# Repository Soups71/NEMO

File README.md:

# NEMO Documentation

Welcome to NEMO—the **NMEA2000 Education and Maritime Operations Platform**.

NEMO is a research platform for exploring at maritime network security. It simulates sensors, sniffs traffic, and demonstrates just how easy you can mess with NMEA2000.

This platform focuses on lowering the bar for getting started with boat hacking. Typically to get started with boat hacking you would need thousands of dollars worth of equipment or a friend with a boat. Thankfully, with NEMO all you need is about 40 dollars.

## What's In Here

### Getting Your Feet Wet
1. **[Project Overview](Documentation/README.md)** - What this is and why boats need better security
2. **[Getting Started](Documentation/Getting_Started.md)** - From zero to flashing firmware
3. **[Operations Guide](Documentation/Operations_Guide.md)** - How to actually use the thing
4. **[FAQ](Documentation/FAQ.md)** - "Why doesn't X work?" answered here

### Understanding the Protocols
1. **[NMEA2000 Protocol](Documentation/NMEA2000.md)** - The marine standard for device communication

### Hardware
1. **[Design Reference](Documentation/PCB_Design.md)** - Schematics, layout, gerbers
2. **[3-D Printed Case](Documentation/Case_Design.md)** - Documentation on the case

### Software
9. **[Source Code Architecture](Documentation/Source_Code_Architecture.md)** - Deep dive into the firmware

### The Fun Part
10. **[Security Research & Attacks](Documentation/Attacks.md)** - How the attacks work and academic context

## Quick Start (TL;DR)

1. Get parts from [Hardware Guide](Documentation/PCB_Design.md)
2. Flash firmware via [Getting Started](Documentation/Getting_Started.md)
3. Learn the UI in [Operations Guide](Documentation/Operations_Guide.md)
4. Break Stuff
5. Profit!

## What This Is For

NEMO exists for:
- **Security researchers** exploring maritime vulnerabilities
- **Students** learning about CAN bus and protocol weaknesses
- **Industry folks** who want to see why NMEA2000 security matters

## Contributing

Found a bug? Got a cool feature idea? Open an issue or send a PR.

Contribution Ideas:
- New PGN support
- Bug fixes
- Documentation improvements

## Contact

Any questions or concerns regarding this project can be sent to nemo@jamescampbell.org

## Disclaimer

Released for educational and research purposes. Don't do crimes with it.

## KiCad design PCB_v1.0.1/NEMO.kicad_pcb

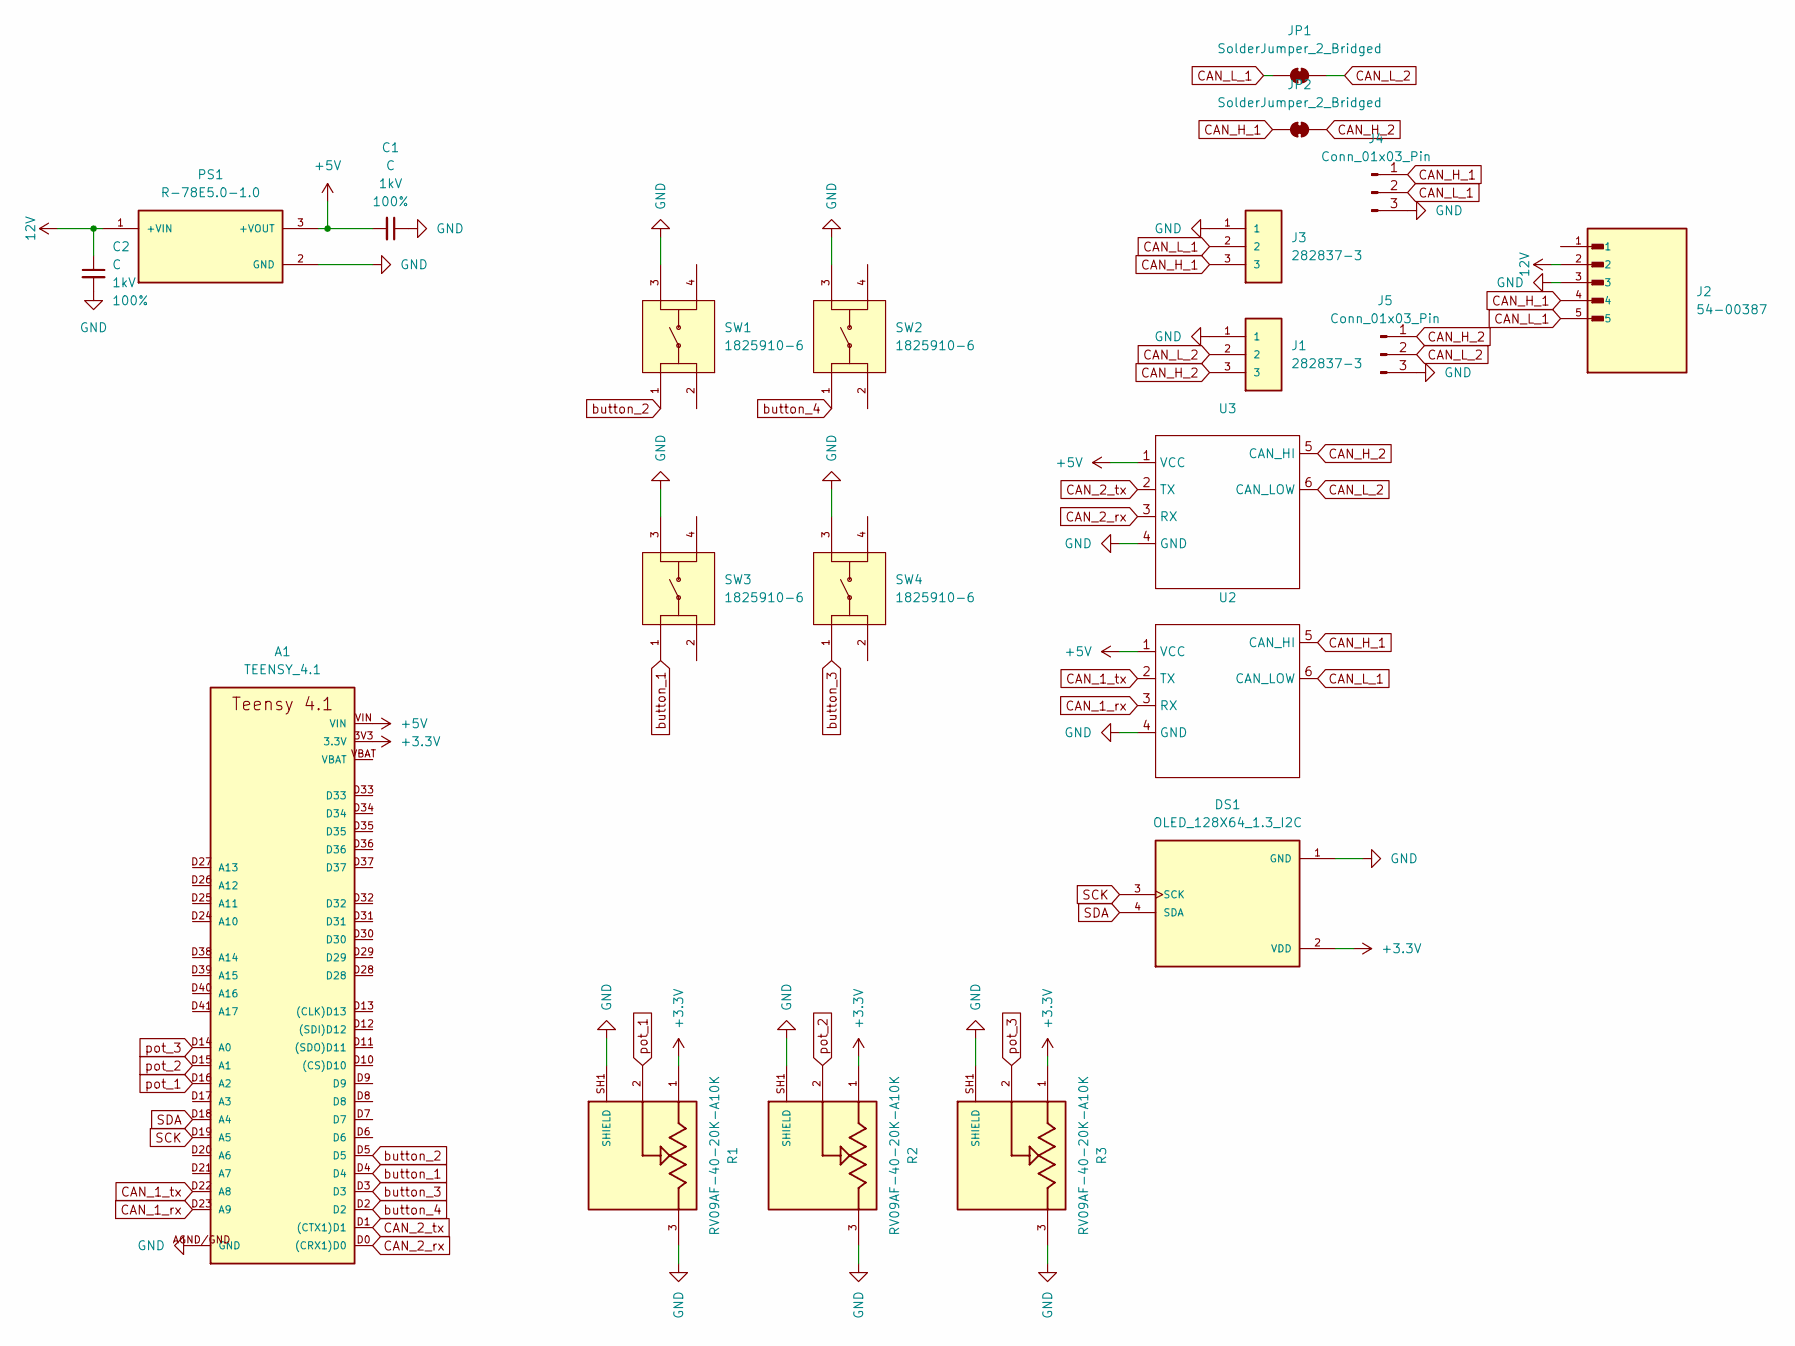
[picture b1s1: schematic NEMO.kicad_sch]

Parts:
A1: TEENSY_4.1; TEENSY_LONG_EXT
C1, C2: C; C_Disc_D9.0mm_W5.0mm_P5.00mm; Voltage 1kV; Tolerance 100%
DS1: OLED_128X64_1.3_I2C; LCD_OLED_128X64_1.3_I2C; PARTREV NA
J1, J3: 282837-3; TE_282837-3; PARTREV H
J2: 54-00387; NMEA2000; PARTREV A
J4, J5: Conn_01x03_Pin; FanPinHeader_1x03_P2.54mm_Vertical
JP1, JP2: SolderJumper_2_Bridged; SolderJumper-2_P1.3mm_Bridged_Pad1.0x1.5mm
PS1: R-78E5.0-1.0; CONV_R-78E5.0-1.0; PARTREV 6
R1, R2, R3: RV09AF-40-20K-A10K; TRIM_RV09AF-40-20K-A10K; PARTREV N/A
SW1, SW2, SW3, SW4: 1825910-6; SW_1825910-6-4; PARTREV C10
U2, U3: CAN_CHIP

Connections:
12V: C2.1, J2.2, PS1.1 (+VIN)
+3.3V: A1.3V3 (3.3V), A1.3V3@2 (3.3V), A1.3V3@3 (3.3V), DS1.2 (VDD), R1.1, R2.1, R3.1
+5V: A1.VIN, C1.2, PS1.3 (+VOUT), U2.1 (VCC), U3.1 (VCC)
CAN_1_rx: A1.D23 (A9), U2.3 (RX)
CAN_1_tx: A1.D22 (A8), U2.2 (TX)
CAN_2_rx: A1.D0 ((CRX1)D0), U3.3 (RX)
CAN_2_tx: A1.D1 ((CTX1)D1), U3.2 (TX)
CAN_H_1: J2.4, J3.3, J4.1, JP2.1 (A), U2.5 (CAN_HI)
CAN_H_2: J1.3, J5.1, JP2.2 (B), U3.5 (CAN_HI)
CAN_L_1: J2.5, J3.2, J4.2, JP1.1 (A), U2.6 (CAN_LOW)
CAN_L_2: J1.2, J5.2, JP1.2 (B), U3.6 (CAN_LOW)
GND: A1.AGND/GND (GND), A1.GND, A1.GND@2 (GND), C1.1, C2.2, DS1.1 (GND), J1.1, J2.3, J3.1, J4.3, J5.3, PS1.2 (GND), R1.3, R1.SH1 (SHIELD), R1.SH2 (SHIELD), R2.3, R2.SH1 (SHIELD), R2.SH2 (SHIELD), R3.3, R3.SH1 (SHIELD), R3.SH2 (SHIELD), SW1.3, SW2.3, SW3.3, SW4.3, U2.4 (GND), U3.4 (GND)
SCK: A1.D19 (A5), DS1.3 (SCK)
SDA: A1.D18 (A4), DS1.4 (SDA)
button_1: A1.D4, SW3.1
button_2: A1.D5, SW1.1
button_3: A1.D3, SW4.1
button_4: A1.D2, SW2.1
pot_1: A1.D16 (A2), R1.2
pot_2: A1.D15 (A1), R2.2
pot_3: A1.D14 (A0), R3.2

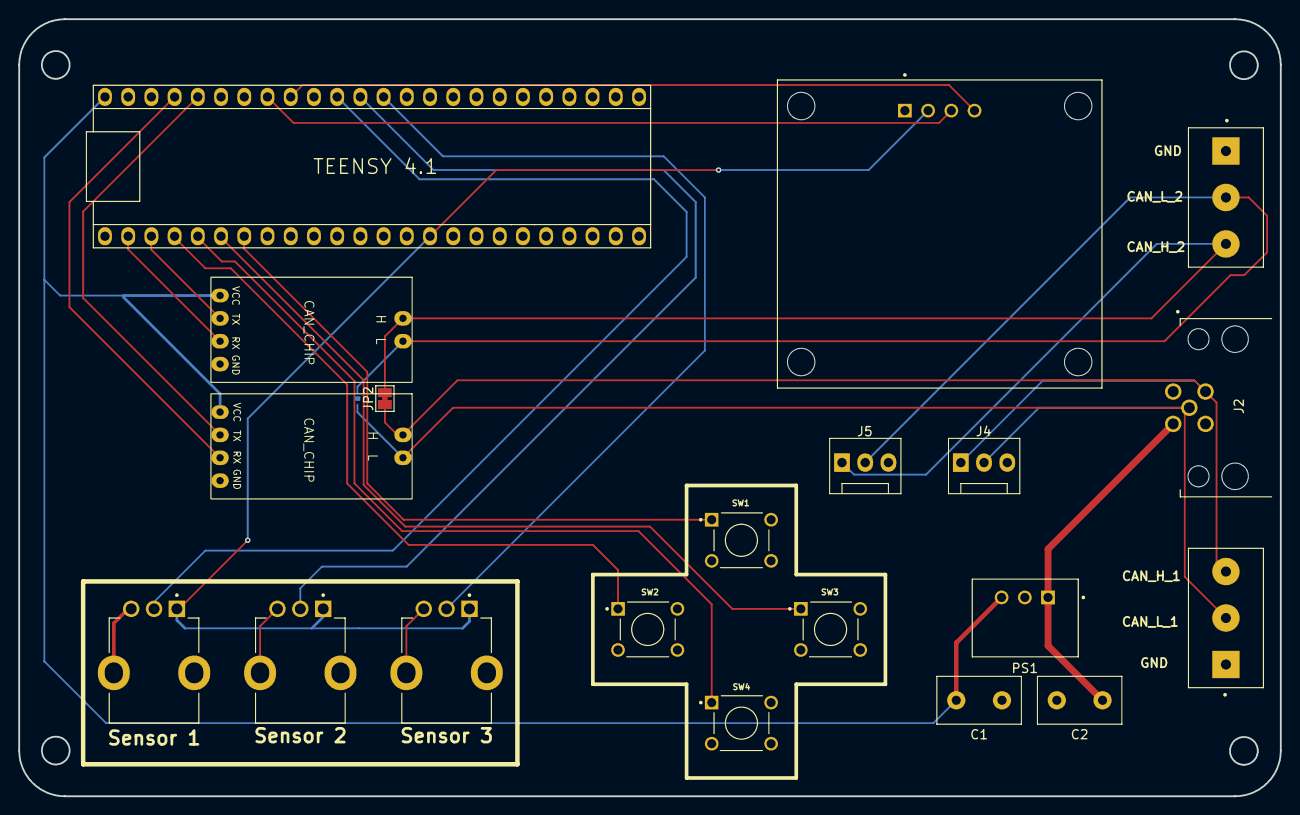
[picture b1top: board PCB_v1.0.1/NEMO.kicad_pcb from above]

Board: 2 copper layers, 138.0 x 85.0 mm, 21 parts (1 on the bottom side), 21 nets.

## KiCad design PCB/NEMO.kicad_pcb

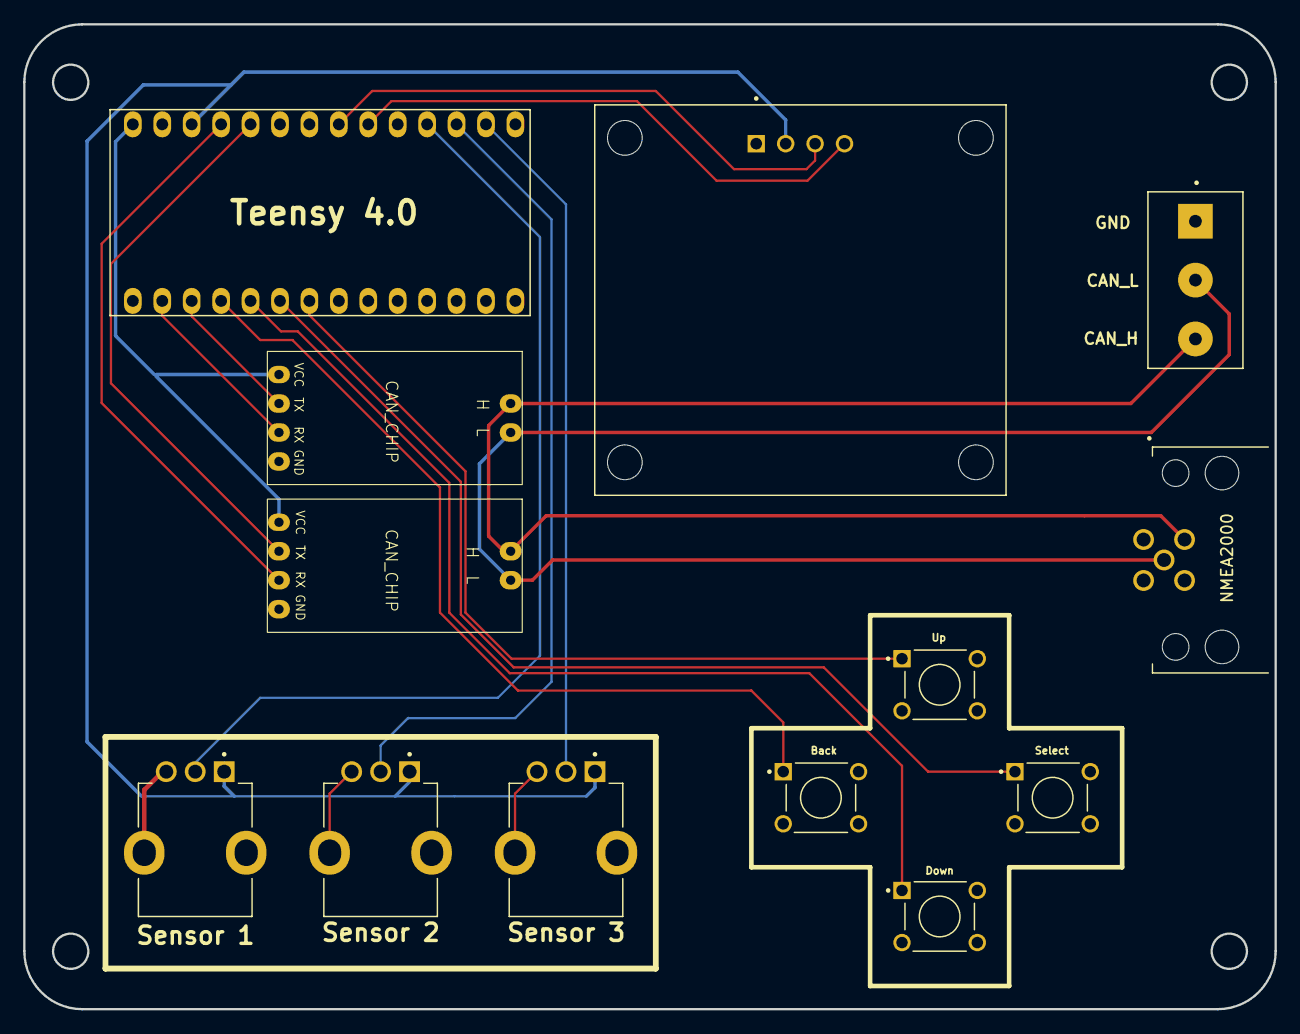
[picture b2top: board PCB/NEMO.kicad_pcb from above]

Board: 2 copper layers, 108.0 x 85.0 mm, 13 parts (0 on the bottom side), 18 nets.

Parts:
Back: 1825910-6; SW_1825910-6-4
DS1: OLED_128X64_1.3_I2C; LCD_OLED_128X64_1.3_I2C
Down: 1825910-6; SW_1825910-6-4
J1: 282837-3; TE_282837-3
NMEA2000: 54-00387; NMEA2000
R1, R2, R3: RV09AF-40-20K-A10K; TRIM_RV09AF-40-20K-A10K
Select: 1825910-6; SW_1825910-6-4
Teensy 4.0: DEV-15583; MODULE_DEV-15583
U2, U3: CAN_CHIP
Up: 1825910-6; SW_1825910-6-4

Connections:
+3.3V: DS1.2 (VDD), R1.1, R2.1, R3.1, Teensy 4.0.3.3V_2
+5V: Teensy 4.0.VIN, U2.1 (VCC), U3.1 (VCC)
CAN_1_rx: Teensy 4.0.23, U2.3 (RX)
CAN_1_tx: Teensy 4.0.22, U2.2 (TX)
CAN_2_rx: Teensy 4.0.0, U3.3 (RX)
CAN_2_tx: Teensy 4.0.1, U3.2 (TX)
CAN_H: J1.3, NMEA2000.4, U2.5 (CAN_HI), U3.5 (CAN_HI)
CAN_L: J1.2, NMEA2000.5, U2.6 (CAN_LOW), U3.6 (CAN_LOW)
GND: Back.3, DS1.1 (GND), Down.3, J1.1, NMEA2000.3, R1.3, R1.SH1 (SHIELD), R1.SH2 (SHIELD), R2.3, R2.SH1 (SHIELD), R2.SH2 (SHIELD), R3.3, R3.SH1 (SHIELD), R3.SH2 (SHIELD), Select.3, Teensy 4.0.G1, Teensy 4.0.G3, U2.4 (GND), U3.4 (GND), Up.3
SCK: DS1.3 (SCK), Teensy 4.0.19
SDA: DS1.4 (SDA), Teensy 4.0.18
button_1: Select.1, Teensy 4.0.4
button_2: Teensy 4.0.5, Up.1
button_3: Down.1, Teensy 4.0.3
button_4: Back.1, Teensy 4.0.2
pot_1: R1.2, Teensy 4.0.16
pot_2: R2.2, Teensy 4.0.15
pot_3: R3.2, Teensy 4.0.14

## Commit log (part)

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2026-01-25 First Release of NEMO
2026-02-17 Fixing broken links
